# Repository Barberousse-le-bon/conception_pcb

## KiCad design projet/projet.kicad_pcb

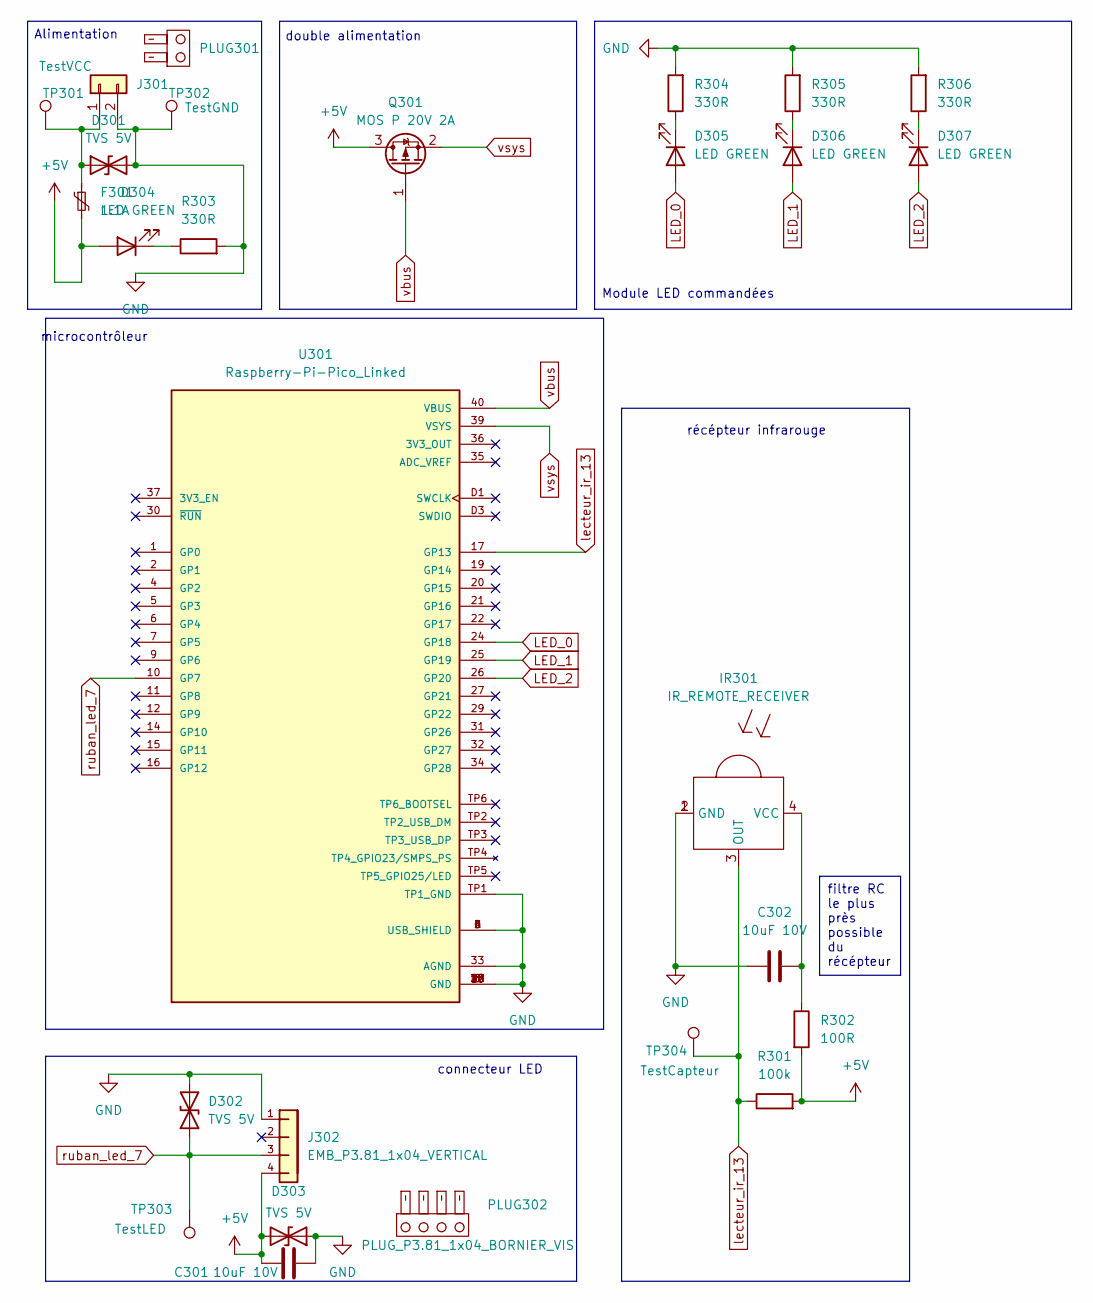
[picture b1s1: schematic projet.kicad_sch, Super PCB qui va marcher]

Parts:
C301, C302: 10uF 10V; C0603; MPN CL10A106MP8NNNC
D301, D302, D303: TVS 5V; SOD323_NP; MPN PSD05C-LF-T7
D304, D305, D306, D307: LED GREEN; LED0805; MPN 150080GS75000
F301: 1.1A; R1812L; MPN 1812L110/24DR
IR301: IR_REMOTE_RECEIVER; SMD-4P_4x5mm; MPN IRM-H638T/TR2
J301: EMB_P3.81_1x02_VERTICAL; Conn_THT_3.81_2x1_Vertical; MPN WJ15EDGVC-3.81-2P
J302: EMB_P3.81_1x04_VERTICAL; Conn_THT_3.81_4x1_Vertical; MPN WJ15EDGVC-3.81-4P
PLUG301: PLUG_P3.81_1x02_BORNIER_VIS; MPN WJ15EDGK-3.81-2P
PLUG302: PLUG_P3.81_1x04_BORNIER_VIS; MPN WJ15EDGK-3.81-4P
Q301: MOS P 20V 2A; SOT23; MPN AP2301B
R301: 100k; R0402; MPN RC0402FR-07100KL
R302: 100R; R0402; MPN RC0402FR-07100RL
R303, R304, R305, R306: 330R; R0603; MPN 0603WAF3300T5E
TP301: TestVCC; TestPoint_Pad_D2.0mm
TP302: TestGND; TestPoint_Pad_D2.0mm
TP303: TestLED; TestPoint_Pad_D2.0mm
TP304: TestCapteur; TestPoint_Pad_D2.0mm
U301: Raspberry-Pi-Pico_Linked; Raspberry-Pi-Pico; MPN Raspberry Pi Pico

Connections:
+5V: C301.1, D303.2 (A2), D304.2 (A), F301.2, J302.4, Q301.3 (D), R301.2, R302.2
GND: C301.2, C302.1, D301.2 (A2), D302.2 (A2), D303.1 (A1), IR301.1 (GND), IR301.2 (GND), J301.2, J302.1, R303.2, R304.2, R305.2, R306.2, TP302.1, U301.3 (GND), U301.8 (GND), U301.13 (GND), U301.18 (GND), U301.23 (GND), U301.28 (GND), U301.33 (AGND), U301.38 (GND), U301.A (USB_SHIELD), U301.B (USB_SHIELD), U301.C (USB_SHIELD), U301.D (USB_SHIELD), U301.D2 (GND), U301.TP1 (TP1_GND)
LED_0: D305.2 (A), U301.24 (GP18)
LED_1: D306.2 (A), U301.25 (GP19)
LED_2: D307.2 (A), U301.26 (GP20)
unnamed: D301.1 (A1), F301.1, J301.1, TP301.1
unnamed: D304.1 (K), R303.1
unnamed: D305.1 (K), R304.1
unnamed: D306.1 (K), R305.1
unnamed: D307.1 (K), R306.1
unnamed: C302.2, IR301.4 (VCC), R302.1
lecteur_ir_13: IR301.3 (OUT), R301.1, TP304.1, U301.17 (GP13)
ruban_led_7: D302.1 (A1), J302.3, TP303.1, U301.10 (GP7)
vbus: Q301.1 (G), U301.40 (VBUS)
vsys: Q301.2 (S), U301.39 (VSYS)

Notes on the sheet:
filtre RC le plus près possible du récépteur
Module LED commandées
Alimentation
connecteur LED
récépteur infrarouge
microcontrôleur
double alimentation

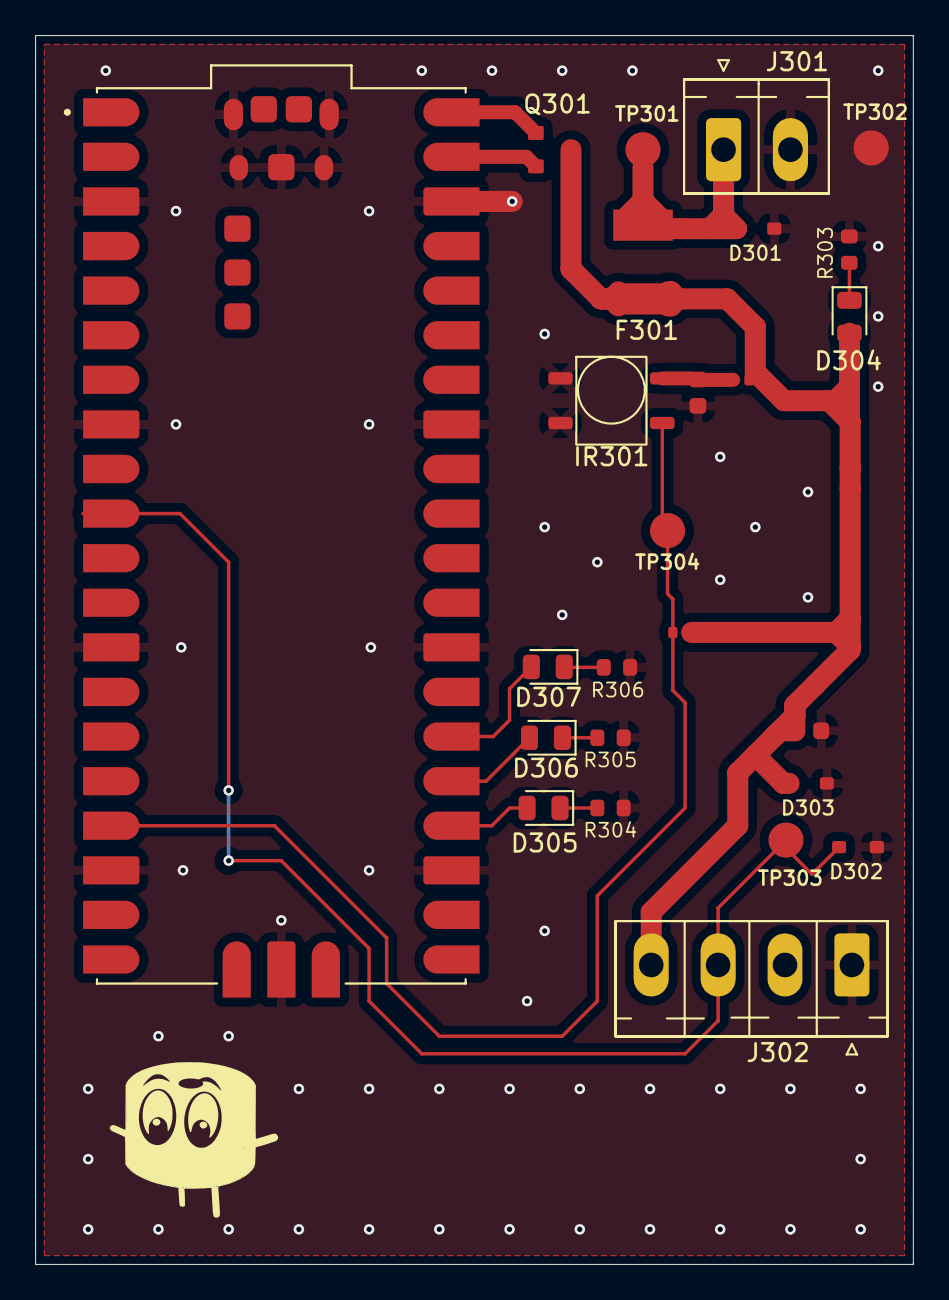
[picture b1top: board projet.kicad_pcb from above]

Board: 2 copper layers, 50.0 x 70.0 mm, 25 parts (0 on the bottom side), 15 nets.

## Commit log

2025-02-06 ajout du projet vide
2025-02-06 premier jet du circuit
2025-02-06 mise à jour du schematic avec les test points et ajout des TVS et inversion vcc gnd sur l'entrée
2025-02-06 ajout des indicateurs de non connection
2025-02-06 ajout du mos pour gérer la double alimentation
2025-02-06 chagement du modèle de raspberry pico pour résoudre des conflits avec l'empreinte
2025-02-06 début Routage
2025-02-06 ajout des capa de découplage
2025-02-06 démarrage routage et installations des ports
2025-02-11 ajout d'un fusible en entrée
2025-02-11 ajout des log
2025-02-11 Première version carte complète
2025-02-11 Correctif des pistes et plan de masse au front
2025-02-11 ajout des images sur le^pcb
2025-02-11 Ajout de graphisme et fichiers de fabrications
2025-02-11 Dernière modifs avant vérif externes
